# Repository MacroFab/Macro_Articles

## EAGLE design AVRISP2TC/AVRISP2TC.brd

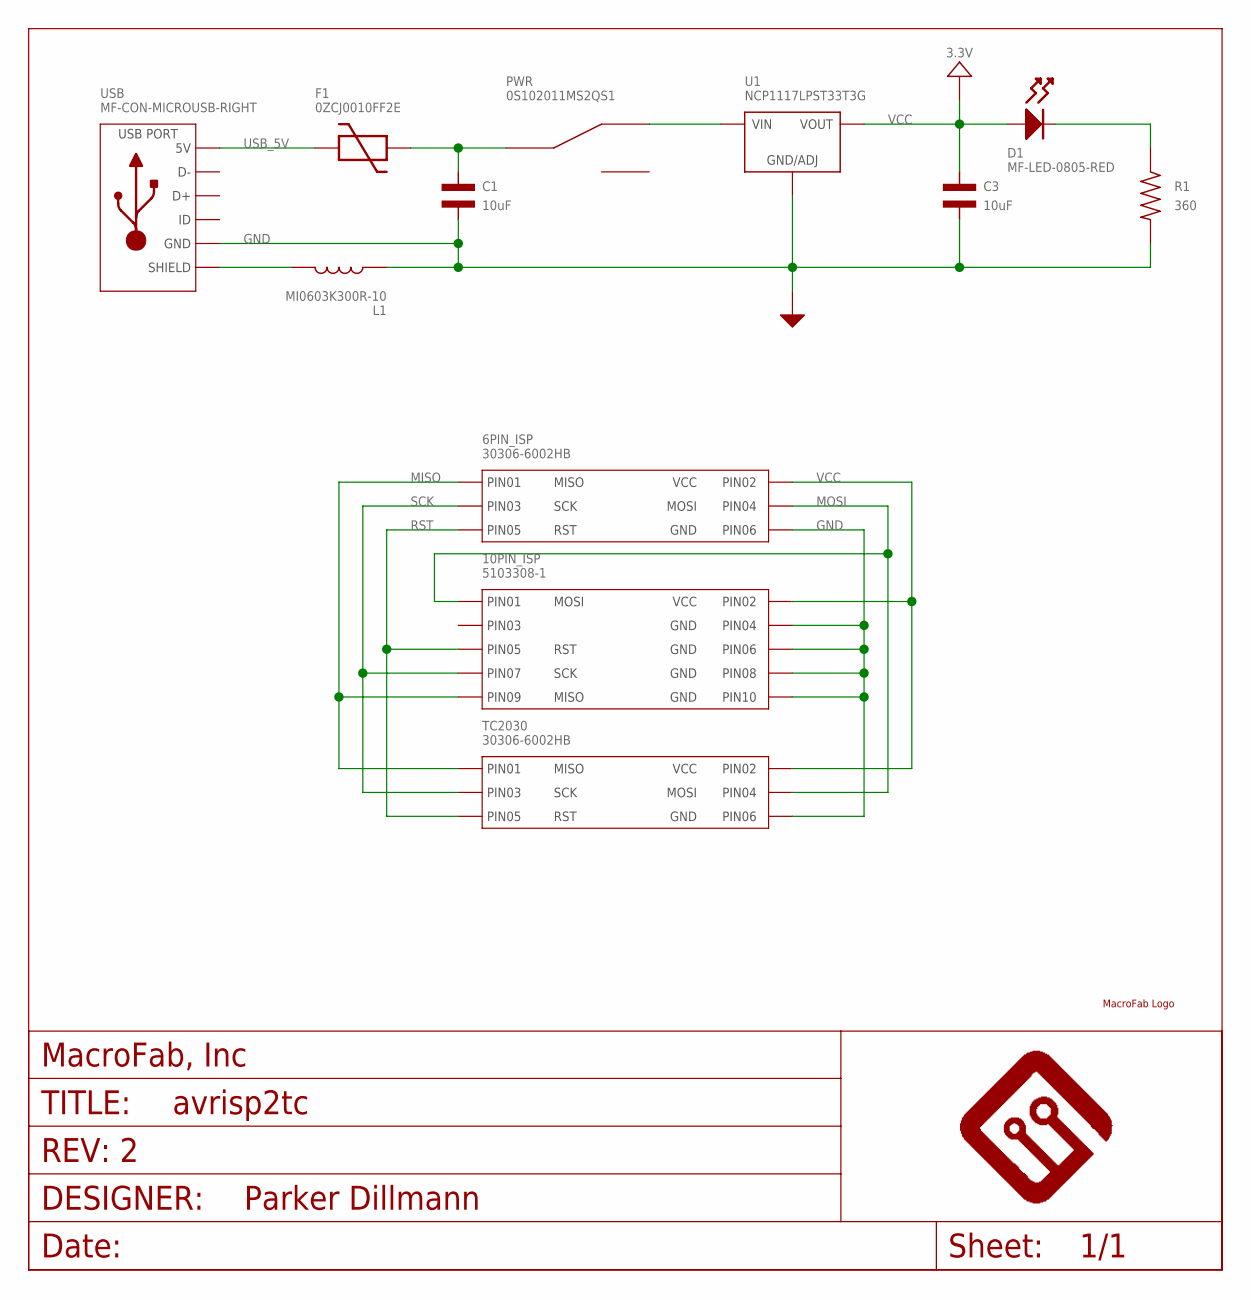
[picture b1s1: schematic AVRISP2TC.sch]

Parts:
6PIN_ISP: 30306-6002HB
10PIN_ISP: 5103308-1
C1, C3: 10uF; C1206; MPN MF-CAP-1206-10uF
D1: MF-LED-0805-RED; LED0805
F1: 0ZCJ0010FF2E; 1206; MPN 0ZCJ0010FF2E
FRAME1: MF_FRAMEDEFAULT; MF_FRAME_DEFAULT
L1: MI0603K300R-10; L0603; MPN MI0603K300R-10
PWR: 0S102011MS2QS1; MPN 0S102011MS2QS1
R1: 360; R0805; MPN MF-RES-0805-360
TC2030: 30306-6002HB
U1: NCP1117LPST33T3G; SOT-223-3
U$3: MF_LOGOLOGO_MEDIUM; MF_LOGO_MEDIUM
USB: MF-CON-MICROUSB-RIGHT; MICROUSB-RIGHT

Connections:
GND: 6PIN_ISP.6 (PIN6), 10PIN_ISP.4 (PIN4), 10PIN_ISP.6 (PIN6), 10PIN_ISP.8 (PIN8), 10PIN_ISP.10 (PIN10), C1.P$2, C3.P$2, L1.P$1, R1.P$2, TC2030.6 (PIN6), U1.P$2 (GND/ADJ), USB.5 (GND)
MISO: 6PIN_ISP.1 (PIN1), 10PIN_ISP.9 (PIN9), TC2030.1 (PIN1)
MOSI: 6PIN_ISP.4 (PIN4), 10PIN_ISP.1 (PIN1), TC2030.4 (PIN4)
unnamed: D1.CATHODE, R1.P$1
unnamed: C1.P$1, F1.2, PWR.2 (C)
unnamed: L1.P$2, USB.S1 (SLD), USB.S2 (SLD), USB.S3 (SLD), USB.S4 (SLD), USB.S5 (SLD), USB.S6 (SLD)
unnamed: PWR.1, U1.P$4 (VIN)
RST: 6PIN_ISP.5 (PIN5), 10PIN_ISP.5 (PIN5), TC2030.5 (PIN5)
SCK: 6PIN_ISP.3 (PIN3), 10PIN_ISP.7 (PIN7), TC2030.3 (PIN3)
USB_5V: F1.1, USB.1 (5V)
VCC: 6PIN_ISP.2 (PIN2), 10PIN_ISP.2 (PIN2), C3.P$1, D1.ANODE, TC2030.2 (PIN2), U1.P$1 (VOUT), U1.P$3 (VOUT)

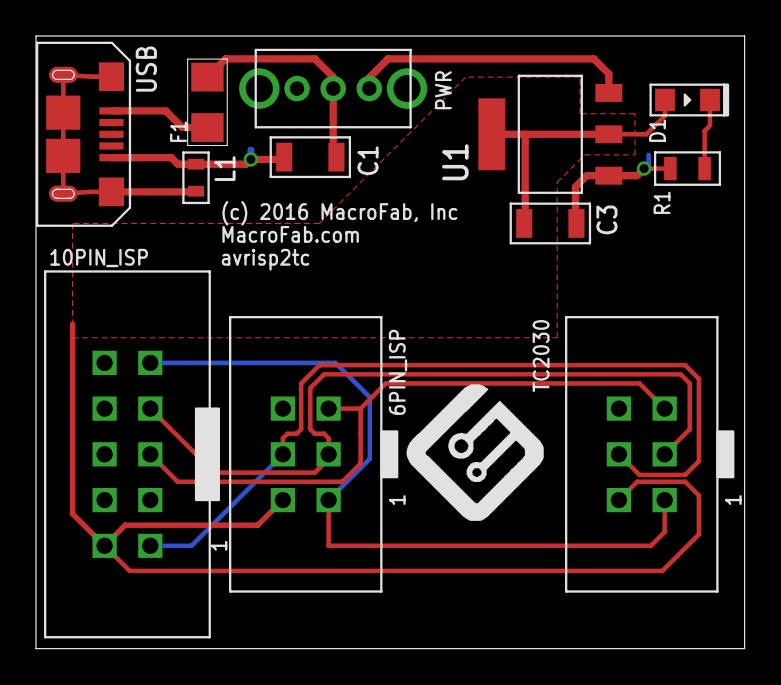
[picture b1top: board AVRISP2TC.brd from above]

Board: 2 copper layers, 39.4 x 34.0 mm, 14 parts (0 on the bottom side), 11 nets.

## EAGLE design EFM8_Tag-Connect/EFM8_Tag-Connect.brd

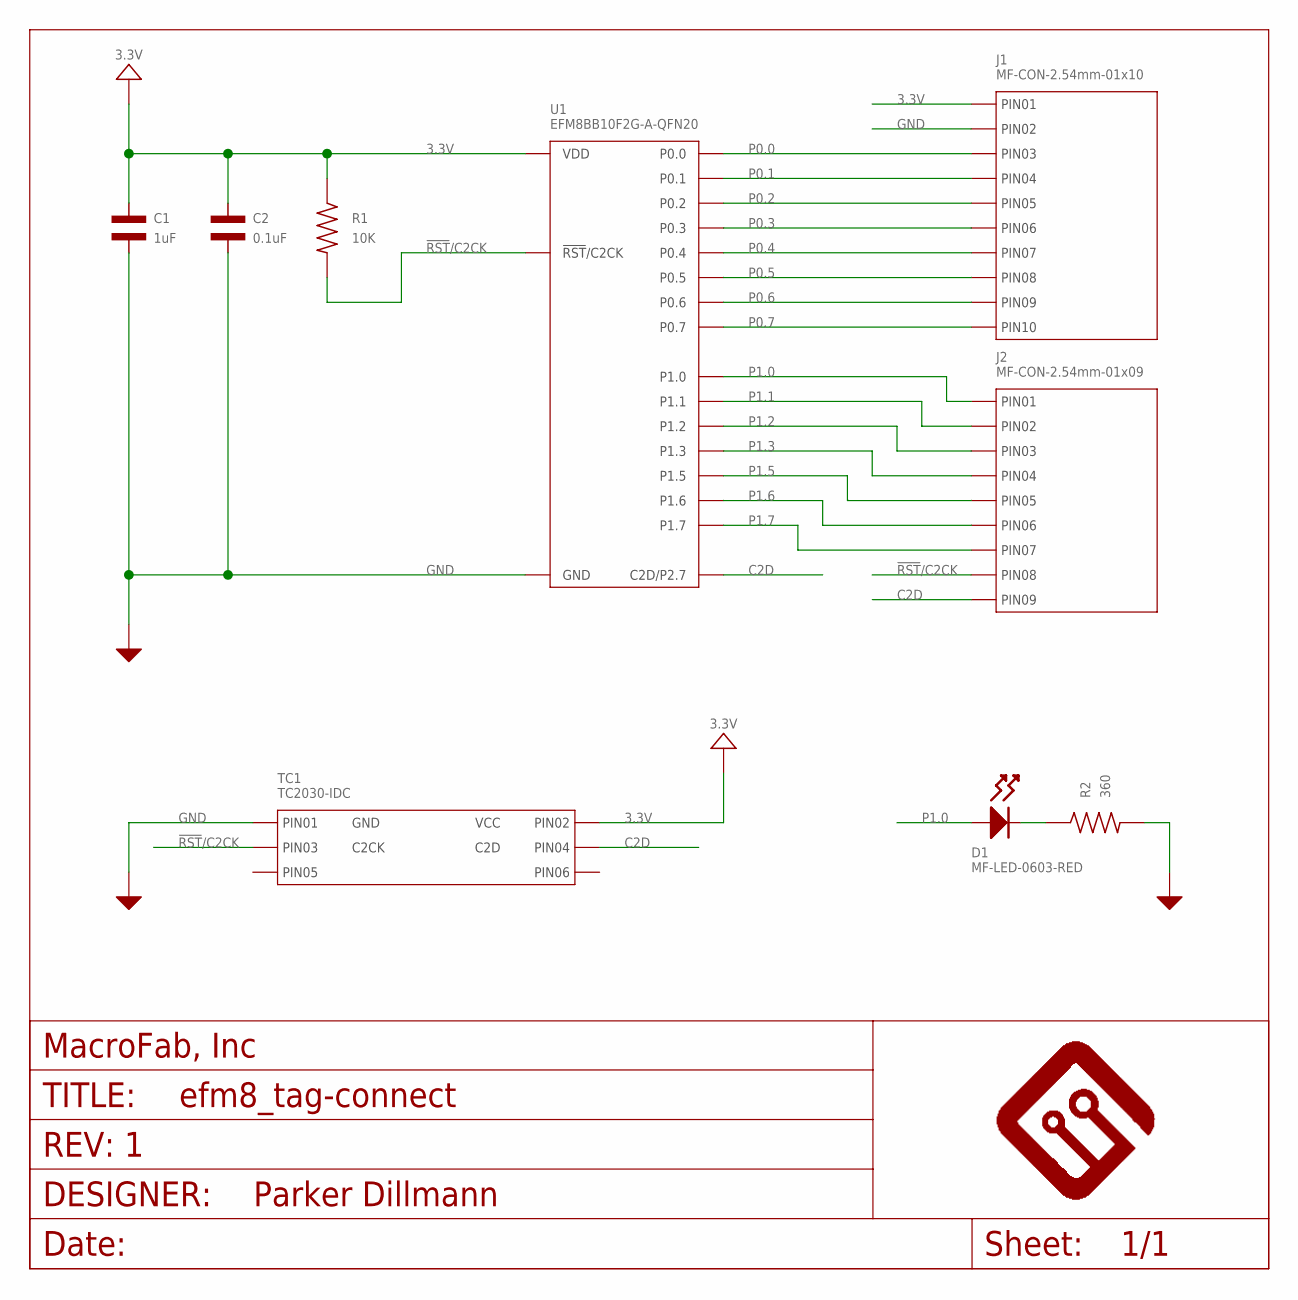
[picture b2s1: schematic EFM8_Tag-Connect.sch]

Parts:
C1: 1uF; C0402; MPN MF-CAP-0402-1uF
C2: 0.1uF; C0402; MPN MF-CAP-0402-0.1uF
D1: MF-LED-0603-RED; LED0603
FRAME1: MF_FRAMEDEFAULT; MF_FRAME_DEFAULT
J1: MF-CON-2.54mm-01x10; PTH_2.54MM_01X10
J2: MF-CON-2.54mm-01x09; PTH_2.54MM_01X09
R1: 10K; R0402; MPN MF-RES-0402-10K
R2: 360; R0402; MPN MF-RES-0402-360
TC1: TC2030-IDC; TC2030-IDC-FP
U1: EFM8BB10F2G-A-QFN20; EFM8BB10F(2/4/8)G-A-QFN20; MPN EFM8BB10F2G-A-QFN20

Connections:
3.3V: C1.P$1, C2.P$1, J1.P$1 (PIN1), R1.P$1, TC1.P$2 (PIN2), U1.P$4 (VDD)
!RST!/C2CK: J2.P$8 (PIN8), R1.P$2, TC1.P$3 (PIN3), U1.P$5 (!RST!/C2CK)
C2D: J2.P$9 (PIN9), TC1.P$4 (PIN4), U1.P$6 (C2D/P2.7)
GND: C1.P$2, C2.P$2, J1.P$2 (PIN2), R2.P$2, TC1.P$1 (PIN1), U1.P$3 (GND), U1.P$12 (GND), U1.PAD (GND)
unnamed: D1.CATHODE, R2.P$1
P0.0: J1.P$3 (PIN3), U1.P$2 (P0.0)
P0.1: J1.P$4 (PIN4), U1.P$1 (P0.1)
P0.2: J1.P$5 (PIN5), U1.P$20 (P0.2)
P0.3: J1.P$6 (PIN6), U1.P$19 (P0.3)
P0.4: J1.P$7 (PIN7), U1.P$18 (P0.4)
P0.5: J1.P$8 (PIN8), U1.P$17 (P0.5)
P0.6: J1.P$9 (PIN9), U1.P$16 (P0.6)
P0.7: J1.P$10 (PIN10), U1.P$15 (P0.7)
P1.0: D1.ANODE, J2.P$1 (PIN1), U1.P$14 (P1.0)
P1.1: J2.P$2 (PIN2), U1.P$13 (P1.1)
P1.2: J2.P$3 (PIN3), U1.P$11 (P1.2)
P1.3: J2.P$4 (PIN4), U1.P$10 (P1.3)
P1.5: J2.P$5 (PIN5), U1.P$8 (P1.5)
P1.6: J2.P$6 (PIN6), U1.P$7 (P1.6)
P1.7: J2.P$7 (PIN7), U1.P$9 (P1.7)

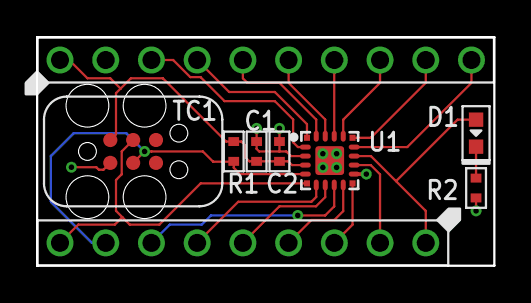
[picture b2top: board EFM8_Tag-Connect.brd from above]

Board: 2 copper layers, 25.4 x 12.7 mm, 10 parts (1 on the bottom side), 20 nets.

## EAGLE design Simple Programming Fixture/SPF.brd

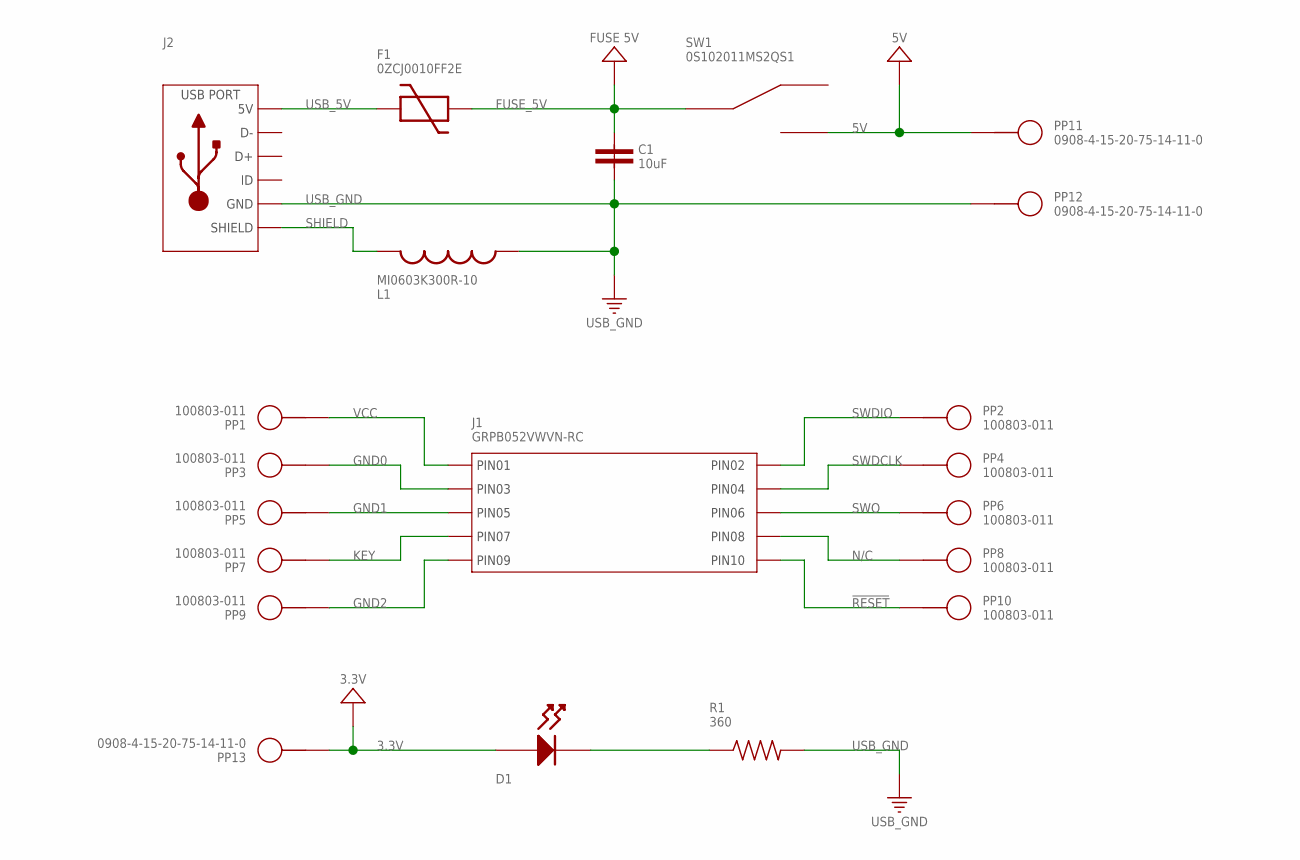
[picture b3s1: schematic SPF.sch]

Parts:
C1: 10uF; 1206
D1: LED_SINGLE_0805; LED0805
F1: 0ZCJ0010FF2E; 1206
J1: GRPB052VWVN-RC
J2: USB_MICRO_RIGHT; MICROUSB-RIGHT
L1: MI0603K300R-10; 0603
PP1, PP2, PP3, PP4, PP5, PP6, PP7, PP8, PP9, PP10: 100803-011; 100803_PROBE
PP11, PP12, PP13: 0908-4-15-20-75-14-11-0
R1: 360; 0805
SW1: 0S102011MS2QS1

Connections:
3.3V: D1.ANODE, PP13.P$1
5V: PP11.P$1, SW1.3 (2)
!RESET: J1.10 (PIN10), PP10.P$1
FUSE_5V: C1.1, F1.2, SW1.2 (C)
GND0: J1.3 (PIN3), PP3.P$1
GND1: J1.5 (PIN5), PP5.P$1
GND2: J1.9 (PIN9), PP9.P$1
KEY: J1.7 (PIN7), PP7.P$1
unnamed: D1.CATHODE, R1.1
N/C: J1.8 (PIN8), PP8.P$1
SHIELD: J2.S1 (SLD), J2.S2 (SLD), J2.S3 (SLD), J2.S4 (SLD), J2.S5 (SLD), J2.S6 (SLD), L1.1
SWDCLK: J1.4 (PIN4), PP4.P$1
SWDIO: J1.2 (PIN2), PP2.P$1
SWO: J1.6 (PIN6), PP6.P$1
USB_5V: F1.1, J2.1 (5V)
USB_GND: C1.2, J2.5 (GND), L1.2, PP12.P$1, R1.2
VCC: J1.1 (PIN1), PP1.P$1

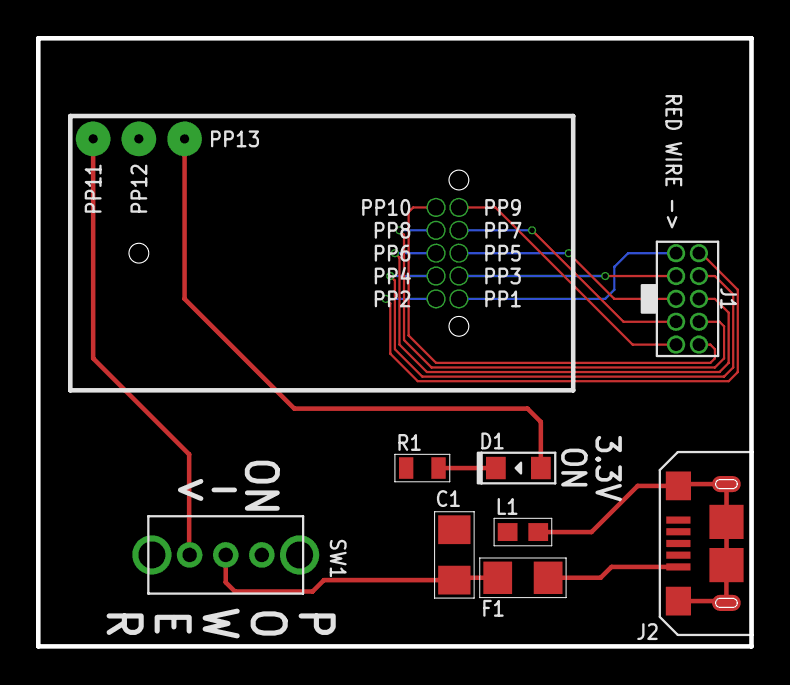
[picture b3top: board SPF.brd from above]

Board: 2 copper layers, 39.6 x 33.8 mm, 21 parts (1 on the bottom side), 17 nets.

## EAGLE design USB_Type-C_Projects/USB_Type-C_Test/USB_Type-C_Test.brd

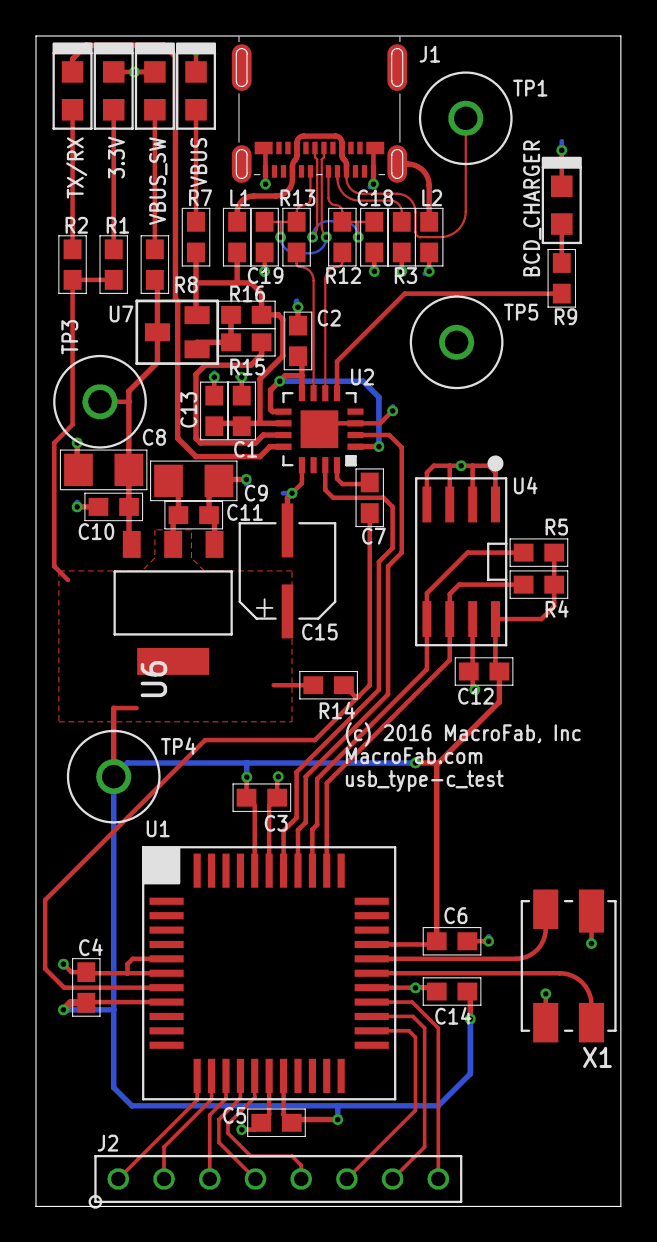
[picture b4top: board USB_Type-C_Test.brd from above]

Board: 2 copper layers, 32.5 x 65.0 mm, 50 parts (0 on the bottom side), 37 nets.

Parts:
3.3V: MF-LED-0805-RED; LED_0805
BCD_CHARGER: MF-LED-0805-RED; LED_0805
C1, C2, C3, C4, C5, C6, C7, C10, C11, C12, C14: .1uF; 0603
C8, C9: 10uF; 1206
C13: 1uF; 0603
C15: 4.7uF; 5MM_CAP_SMD
C18, C19: 47pF; 0603
FRAME1: MF_FRAME_DEFAULT
J1: 105450-0101
J2: 2.54MM_01X08_PIN_HEADER
L1, L2: MI0603K300R-10; 0603
R1, R2, R9: 150; 0603
R3: 5.1K; 0603
R4, R5, R14: 10K; 0603
R7, R8: 330; 0603
R12, R13: 27; 0603
R15: 1K; 0603
R16: 100K; 0603
TP1, TP3, TP4, TP5: KEYSTONE_5115-5119
TX/RX: MF-LED-0805-RED; LED_0805
U1: P8X32A-Q44; P8X32A_LQFP-44
U2: FT230XQ-R; FT230X_QFN-16
U4: CAT24C512WI-GT3; SOIC-8_W
U6: NCP1117LPST33T3G; SOT-223-3
U7: IRLML6401TRPBF; SOT-23-3
VBUS: MF-LED-0805-RED; LED_0805
VBUS_SW: MF-LED-0805-RED; LED_0805
X1: ABMM-6.000MHZ-B2-T; 7MMX5MM

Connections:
3.3V: C3.2, C4.2, C5.2, C6.2, C9.1, C11.1, C12.2, C14.2, C15.P, R1.2, R2.2, R4.2, R5.2, R14.2, TP4.P$1, U1.8, U1.18, U1.30, U1.40, U4.8, U6.P$1, U6.P$3
3V3OUT: C2.1, U2.1, U2.8, U2.9
BCD_CHARGER: R9.2, U2.5
D+: C18.1, J1.A6, J1.B6, R12.2
D-: C19.1, J1.A7, J1.B7, R13.2
GND: 3.3V.CATHODE, BCD_CHARGER.CATHODE, C1.2, C2.2, C3.1, C4.1, C5.1, C6.1, C8.2, C9.2, C10.2, C11.2, C12.1, C13.2, C14.1, C15.N, C18.2, C19.2, J1.A1, J1.A12, J1.B1, J1.B12, L2.2, R3.2, TP5.P$1, U1.5, U1.6, U1.17, U1.27, U1.39, U2.3, U2.13, U2.PAD, U4.1, U4.2, U4.3, U4.4, U4.7, U6.P$2, VBUS.CATHODE, VBUS_SW.CATHODE, X1.P$2, X1.P$4
unnamed: 3.3V.ANODE, R1.1
unnamed: R2.1, TX/RX.ANODE
unnamed: BCD_CHARGER.ANODE, R9.1
unnamed: J1.S_T1, J1.S_T2, J1.S_T3, J1.S_T4, L2.1
unnamed: J1.A5, R3.1
unnamed: R8.1, VBUS_SW.ANODE
unnamed: R7.1, VBUS.ANODE
unnamed: R15.1, R16.1, U7.1
P11: J2.1, U1.12
P12: J2.2, U1.13
P13: J2.3, U1.14
P14: J2.4, U1.15
P15: J2.5, U1.16
P21: J2.6, U1.24
P22: J2.7, U1.25
P23: J2.8, U1.26
PWREN: R15.2, U2.11
RES: C7.2, R14.1, U1.7
RTS: C7.1, U2.16
RX: U1.37, U2.2
SCL: R4.1, U1.35, U4.6
SDA: R5.1, U1.36, U4.5
TX: U1.38, U2.15
TX_RX_LED: TX/RX.CATHODE, U2.12
USBDM: R13.1, U2.7
USBDP: R12.1, U2.6
VBUS: J1.A4, J1.A9, J1.B4, J1.B9, L1.1, TP1.P$1
VBUS_P1: C1.1, C13.1, L1.2, R7.2, R16.2, U2.10, U7.2
VBUS_SW: C8.1, C10.1, R8.2, TP3.P$1, U6.P$4, U7.3
X0: U1.29, X1.P$3
X1: U1.28, X1.P$1

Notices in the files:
parts and their libraries:
MF_Aesthetics: (c) 2016 MacroFab, Inc
